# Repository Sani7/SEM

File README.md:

# SEM
## Project Files
[pdf](./LaTEX/Practice_Enterprise.pdf)

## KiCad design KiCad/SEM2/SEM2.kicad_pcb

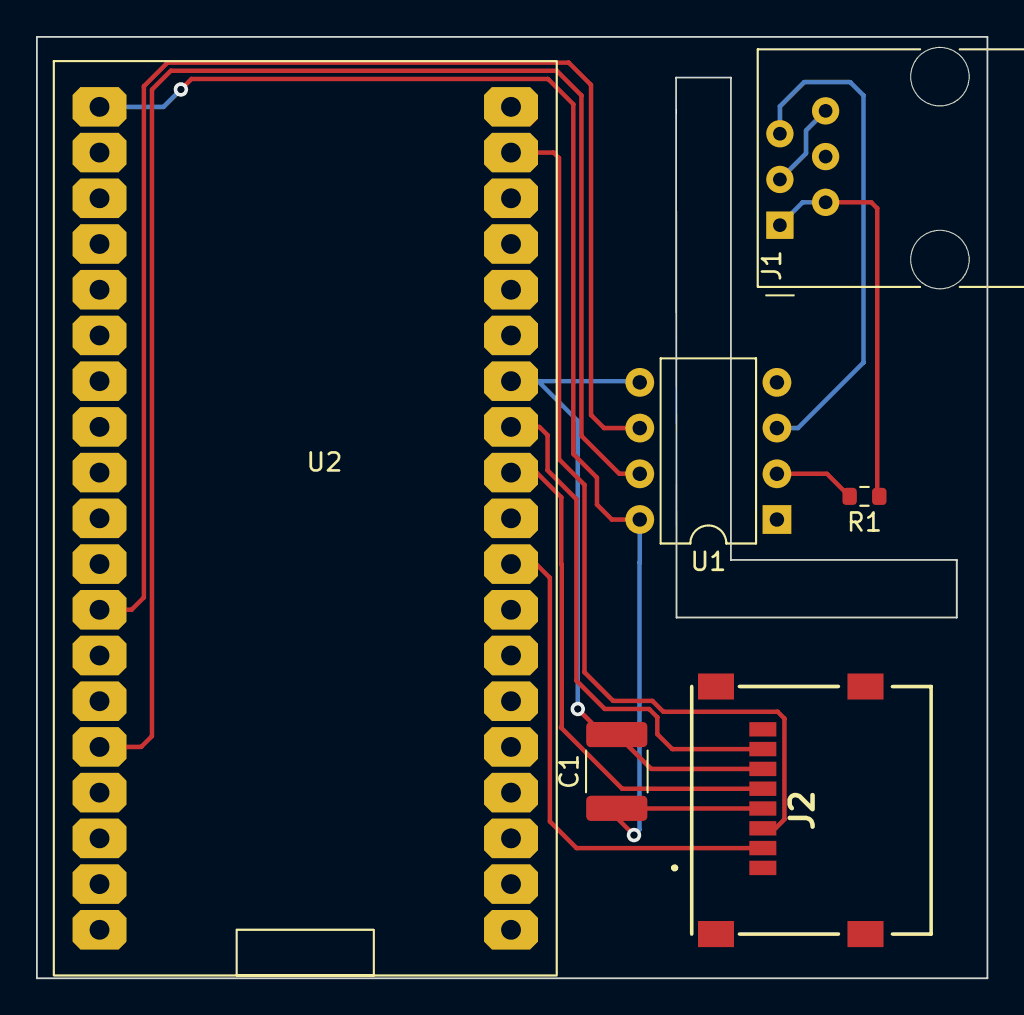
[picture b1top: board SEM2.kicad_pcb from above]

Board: 2 copper layers, 52.8 x 52.3 mm, 6 parts (0 on the bottom side), 12 nets.

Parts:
C1: 0.1u; C_1812_4532Metric
J1: RJ12; RJ12_Amphenol_54601
J2: Micro_SD_Card; 5009010801
R1: 330R; R_0603_1608Metric
U1: 6N137; DIP-8_W7.62mm
U2: ESP32-DevBoard

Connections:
+3V3: C1.1, J2.4 (VDD), U1.8 (VCC), U2.1 (VDD)
+5VA: J1.1, J1.2, R1.1
Data: U1.6 (VO), U2.12 (IO14)
GND: C1.2, J2.6 (VSS), U1.5 (GND), U2.14 (GND), U2.32 (GND), U2.38 (GND)
GND1: J1.3, J1.6
unnamed: R1.2, U1.2 (A)
unnamed: J1.5, U1.3 (C)
Request: U1.7 (EN), U2.15 (IO13)
SD-CS: J2.2 (DAT3/CD), U2.28 (IO17)
VSPI-MISO: J2.7 (DAT0), U2.31 (IO19)
VSPI-MOSI: J2.3 (CMD), U2.37 (IO23)
VSPI-SCLK: J2.5 (CLK), U2.30 (IO18)

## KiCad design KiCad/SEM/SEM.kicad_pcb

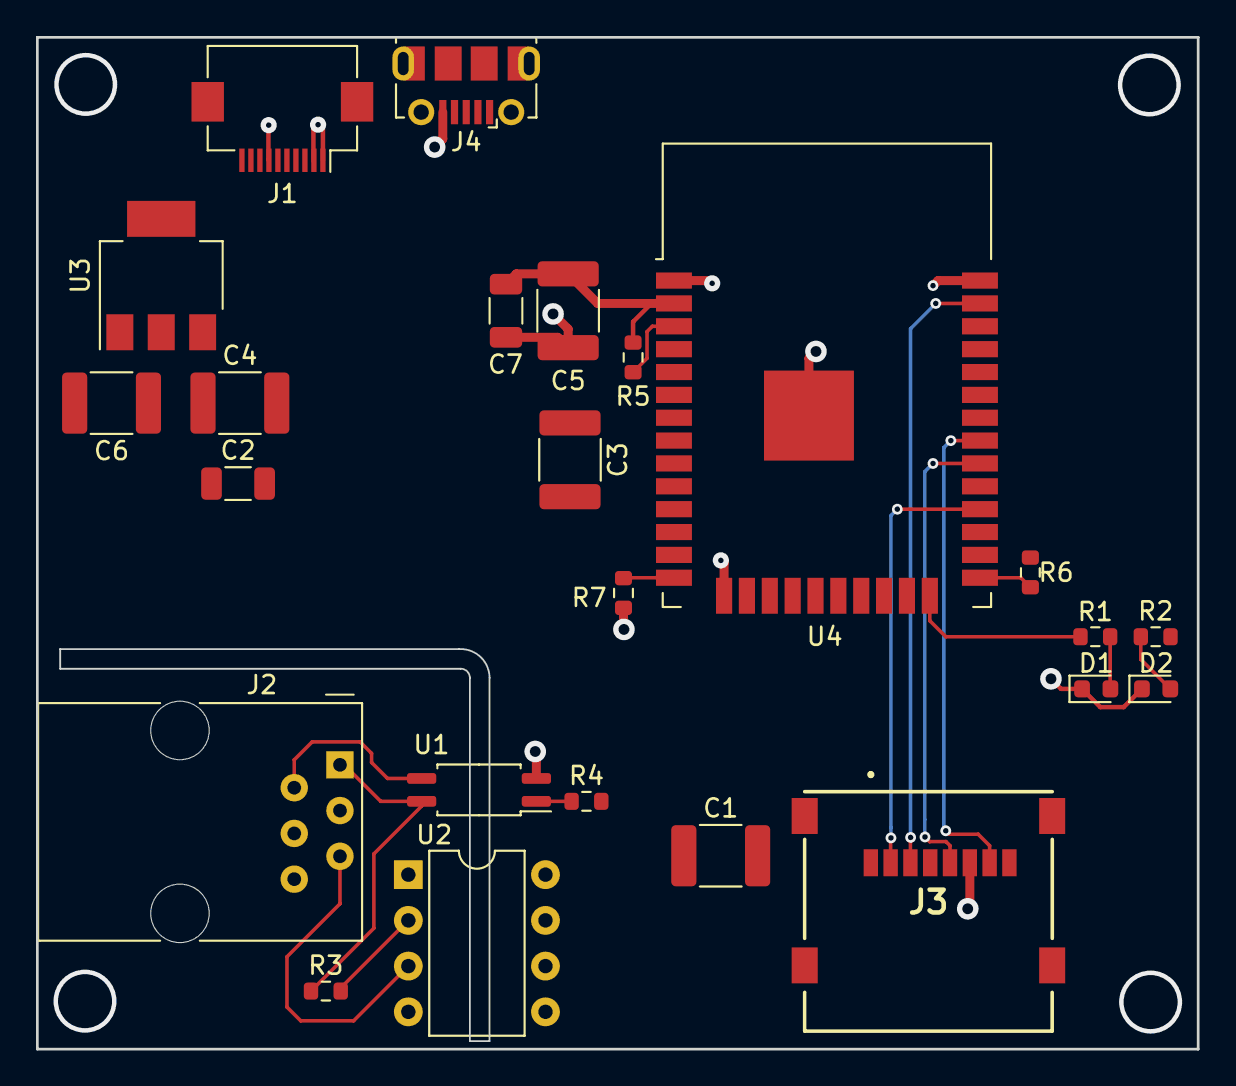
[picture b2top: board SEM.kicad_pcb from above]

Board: 2 copper layers, 64.5 x 56.2 mm, 24 parts (0 on the bottom side), 23 nets.

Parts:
C1, C4, C5: 0.1u; C_1812_4532Metric
C2, C7: 10u; C_1206_3216Metric
C3: 1u; C_1812_4532Metric
C6: 22u; C_1812_4532Metric
D1: Blue; LED_0603_1608Metric
D2: Red; LED_0603_1608Metric
J1: FPC_01x10; Hirose_FH12-10S-0.5SH_1x10-1MP_P0.50mm_Horizontal
J2: RJ12; RJ12_Amphenol_54601
J3: Micro_SD_Card; 5009010801
J4: USB_B_Micro; USB_Micro-B_Molex-105017-0001
R1: 470R; R_0603_1608Metric
R2: 1K; R_0603_1608Metric
R3: 330R; R_0603_1608Metric
R4, R5, R6, R7: 10K; R_0603_1608Metric
U1: ACPL-214-500E; SOP-4_4.4x2.6mm_P1.27mm
U2: 6N137; DIP-8_W7.62mm
U3: AMS1117-3.3; SOT-223-3_TabPin2
U4: ESP32-WROOM-32

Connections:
+3V3: C1.1, C5.1, C6.1, C7.1, J3.4 (VDD), R2.2, R5.1, R6.1, U2.8 (VCC), U3.2 (VO), U4.2 (VDD)
+5V: C2.1, C4.1, J1.9, J1.10, J4.1 (VBUS), U3.3 (VI)
+5VA: J2.1, R3.1, U1.4
BOOT: J1.4, R6.2, U4.25 (IO0)
Data: U2.6 (VO), U4.13 (IO14)
GND: C1.2, C2.2, C3.2, C4.2, C5.2, C6.2, C7.2, D1.1 (K), D2.1 (K), J1.1, J1.2, J1.7, J3.6 (VSS), J4.5 (GND), R7.2, U1.2, U2.5 (GND), U2.7 (EN), U3.1 (GND), U4.1 (GND), U4.15 (GND), U4.38 (GND), U4.39 (GND)
GPIO16: J1.8, U4.27 (IO16)
LED_ACT: R1.2, U4.24 (IO2)
unnamed: D1.2 (A), R1.1
unnamed: D2.2 (A), R2.1
unnamed: J2.2, U1.3
unnamed: J2.5, U2.3 (C)
unnamed: R3.2, U2.2 (A)
unnamed: R4.1, U1.1
unnamed: R7.1, U4.14 (IO12)
RST: C3.1, J1.3, R5.2, U4.3 (EN)
RX0: J1.6, U4.34 (RXD0/IO3)
RXP: J1.5, U4.35 (TXD0/IO1)
Request: R4.2, U4.16 (IO13)
SD-CS: J3.2 (DAT3/CD), U4.28 (IO17)
VSPI-MISO: J3.7 (DAT0), U4.31 (IO19)
VSPI-MOSI: J3.3 (CMD), U4.37 (IO23)
VSPI-SCLK: J3.5 (CLK), U4.30 (IO18)

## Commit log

2022-01-17 Logic spoof
    Did a logic spoof of the test program of the e-paper display
2022-01-17 Block-diagram
    First version of my Block-diagram
2022-01-17 Added some datasheets
2022-01-17 LaTEX
    Started working on my LaTEX document
2022-01-17 Started KiCad designs
    Start Schematic design
2022-01-17 Added the epd3in7 lib
2022-05-19 Added and cleaned some of the Datasheets
2022-05-19 Moved some files to there right place
2022-05-19 Edited the LaTEX document
2022-05-19 Updated the KICAD design files
    PCB is still WIP
2022-05-27 Update .gitignore to ignore build folders
2022-05-27 Add sensor program (untested)
    version 1
2022-05-27 Kicad backups
2022-05-29 Added test code for another esp32
    This code simulates a datagram from a fluvius smart meter
2022-05-29 Update sensor program
    V1.1
    Tested everything except the http post
2022-05-29 Update sensor program
    V1.2
    Fully tested and working
2022-05-29 Remove DS
2022-05-29 Update sensor program
    V1.3
    Added comments
2022-05-29 Edited the LaTEX Doc
2022-05-29 Added presentation & Updated readme to point to my project files
2022-05-29 Finalize the LaTEX Doc
2022-07-07 Added ToDo file
2022-07-07 KiCAD update
2022-07-08 Update todo
2022-08-26 Update code
    V1.4
    Update compile error in http.c and added include of esp_timer.h header file to IoTFluviusMeterReader.h
2022-08-26 Update the LaTEX Doc
2022-08-26 Update KiCAD design
2022-08-28 Update code
    V1.5
    Make uart_init more usefull for other situations
    Fix bad datagram, meter uses \r\n instead of \n
2022-08-28 Update Code
    V1.5.1
    Try to fix the faulty delay
    Let's see next morning
2022-08-30 Last final touches
2022-10-08 Code error fix
    mixed up Consumption High and low tarrif in post querry, not critical and fixed it upstream in grafana with an alias
2022-10-09 Last fixes
2023-03-28 Change WiFi fail behaviour
    Make it so that the esp reboots after the amount of failed wifi connection attempts
2023-06-13 Last fix
2024-03-07 Fix for new version of esp-idf
